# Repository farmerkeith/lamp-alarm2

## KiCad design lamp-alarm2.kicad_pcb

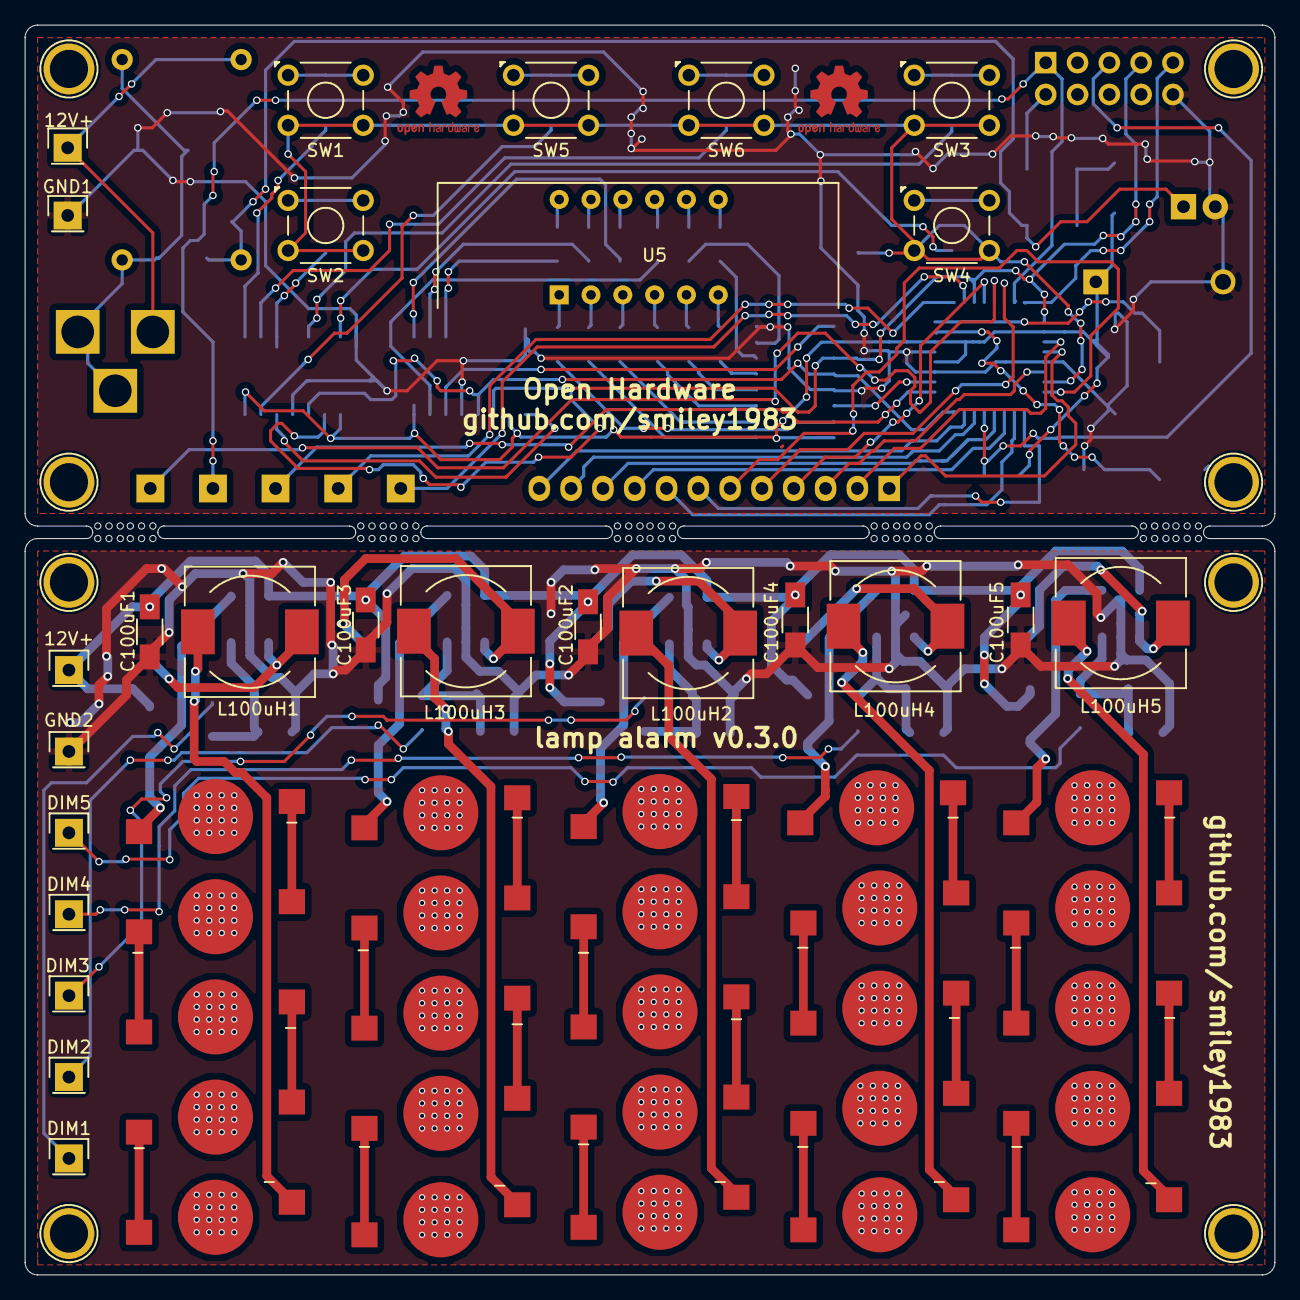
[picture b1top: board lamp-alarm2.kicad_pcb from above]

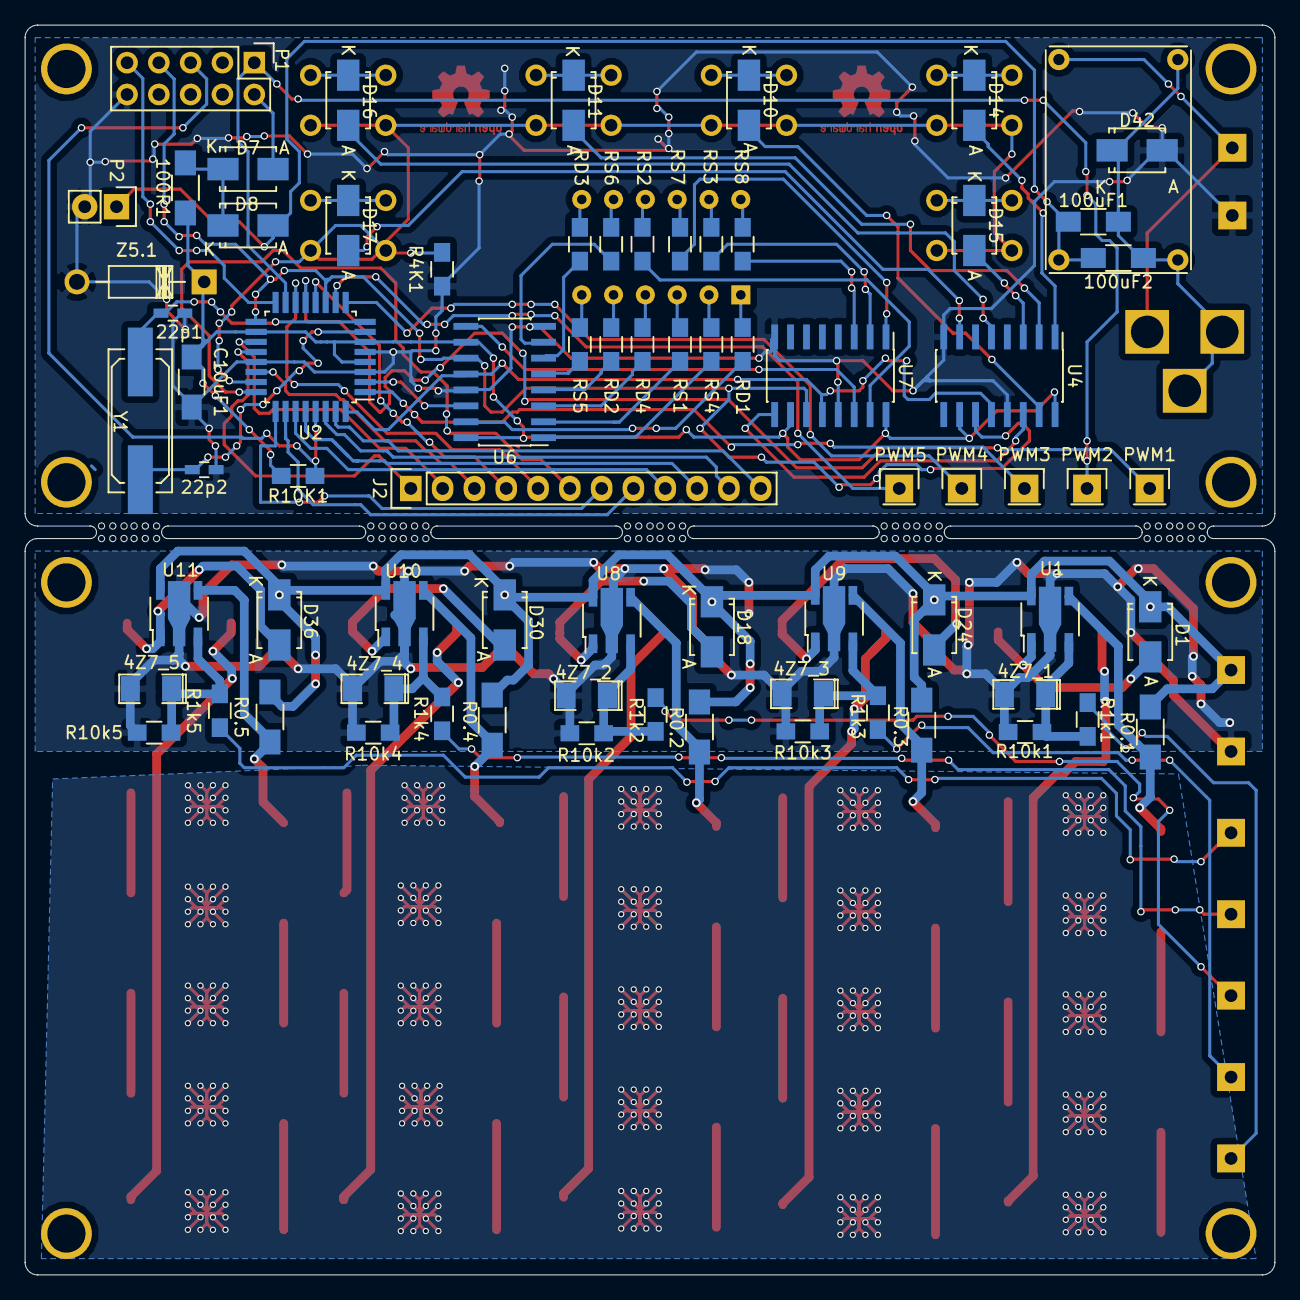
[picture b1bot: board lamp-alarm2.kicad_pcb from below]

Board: 2 copper layers, 99.8 x 99.8 mm, 126 parts (74 on the bottom side), 118 nets.

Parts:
4Z7_1, 4Z7_2, 4Z7_3, 4Z7_4, 4Z7_5: D_Zener_Small; SMD-1206_Pol
12V+, 12V+#2: TEST_1P; Pin_Header_Straight_1x01
22p1, 22p2: C_Small; C_0603_HandSoldering
100R1: R; R_1206_HandSoldering
100uF1, 100uF2: C_Small; C_1206_HandSoldering
-: LED_PAD; 3w_led
-#2, -#3, -#4, -#5, -#6, -#7, -#8, -#9, -#10, -#11, -#12, -#13, -#14, -#15, -#16, -#17, -#18, -#19, -#20, -#21, -#22, -#23, -#24, -#25: LED_PAD; 3w_led
C10uF1, C100uF1, C100uF2, C100uF3, C100uF4, C100uF5: C_Small; C_1206_HandSoldering
D1, D18, D24, D30, D36: D; SMA_Standard_noadhesive
D7, D8, D10, D11, D14, D15, D16, D17, D42: D_Schottky_Small; SMA_Standard_noadhesive
DIM1, DIM2, DIM3, DIM4, DIM5: TEST_1P; Pin_Header_Straight_1x01
GND1, GND2: TEST_1P; Pin_Header_Straight_1x01
J1: Barrel_Jack; BARREL_JACK_nosilk
J2: Conn_01x12; Pin_Header_Straight_1x12
L100uH1, L100uH2, L100uH3, L100uH4, L100uH5: L; Choke_SMD_10.4x10.4_H4.8
P1: CONN_02X05; Pin_Header_Straight_2x05
P2: CONN_01X02; Pin_Header_Straight_1x02
PWM1, PWM2, PWM3, PWM4, PWM5: TEST_1P; Pin_Header_Straight_1x01
R0.1, R0.2, R0.3, R0.4, R0.5: R; R_1206_HandSoldering
R1k1, R1k2, R1k3, R1k4, R1k5, R4K1, R10K1, R10k1, R10k2, R10k3, R10k4, R10k5: R; R_0805_HandSoldering
RD1, RD2, RD3, RD4: R; R_0805_HandSoldering
RS1, RS2, RS3, RS4, RS5, RS6, RS7, RS8: R; R_0805_HandSoldering
SW1, SW2, SW3, SW4, SW5, SW6: SW_PUSH_SMALL_H; tact_switch_6x6
U1, U8, U9, U10, U11: MADW__PT4115-SOT89-5; SOT89-5_Housing
U2: ATMEGA328P-AU; TQFP-32_7x7mm_Pitch0.8mm_narrowerpads
U3: BUCK_1A
U4, U6, U7: 74HC595; SOIC-16_3.9x9.9mm_Pitch1.27mm-narrowerpads
U5: Display_7Seg_Cathode_YY2841AH-33; 7Segment_12pin_1cm_high
Y1: Crystal_Small; Q_49U3HMS
Z5.1: ZENER; Diode_DO-41_SOD81_Horizontal_RM10

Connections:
/HEAT: -.3, -#2.3, -#3.3, -#4.3, -#5.3, -#6.3, -#7.3, -#8.3, -#9.3, -#10.3, -#11.3, -#12.3, -#13.3, -#14.3, -#15.3, -#16.3, -#17.3, -#18.3, -#19.3, -#20.3, -#21.3, -#22.3, -#23.3, -#24.3, -#25.3
/HGND: 4Z7_1.2, 4Z7_2.2, 4Z7_3.2, 4Z7_4.2, 4Z7_5.2, C100uF1.2, C100uF2.2, C100uF3.2, C100uF4.2, C100uF5.2, GND2.1, R10k1.2, R10k2.2, R10k3.2, R10k4.2, R10k5.2, U1.2, U8.2, U9.2, U10.2, U11.2
/LED/LED+: -#25.2, R0.1.1, U1.4
/LED/LED-: -#22.1, L100uH1.1
/PWM0: DIM1.1, R1k1.1
/PWM1: DIM2.1, R1k3.1
/PWM2: DIM3.1, R1k2.1
/PWM3: DIM4.1, R1k4.1
/PWM4: DIM5.1, R1k5.1
/Power/GND_IN: 100uF1.1, 100uF2.1, D42.1, J1.2, J1.3, U3.2, U3.4
/Power/V+: 12V+.1, J1.1, U3.1
/Sheet59CCFEA9/5V_IN: 100uF1.2, 100uF2.2, D8.2, P2.1, U3.3
/Sheet59CCFEA9/ADC6: J2.2, U2.19
/Sheet59CCFEA9/ADC7: J2.3, U2.22
/Sheet59CCFEA9/AREF: J2.1, U2.20
/Sheet59CCFEA9/BTN: R4K1.2, SW1.2, SW2.2, SW3.2, SW4.2, SW5.2, SW6.2, U2.23
/Sheet59CCFEA9/LATCH: U2.32, U4.12, U6.12, U7.12
/Sheet59CCFEA9/MISO: P1.9, U2.16
/Sheet59CCFEA9/PB0: J2.4, U2.12
/Sheet59CCFEA9/PC1: J2.6, U2.24
/Sheet59CCFEA9/PC2: J2.7, U2.25
/Sheet59CCFEA9/PC3: J2.8, U2.26
/Sheet59CCFEA9/PC4: J2.9, U2.27
/Sheet59CCFEA9/PC5: J2.10, U2.28
/Sheet59CCFEA9/PD0: J2.11, U2.30
/Sheet59CCFEA9/PD1: J2.12, U2.31
/Sheet59CCFEA9/PWM0: PWM1.1, U2.13
/Sheet59CCFEA9/PWM1: P1.1, PWM2.1, U2.15
/Sheet59CCFEA9/PWM2: PWM3.1, U2.1
/Sheet59CCFEA9/PWM3: PWM4.1, U2.9
/Sheet59CCFEA9/PWM4: PWM5.1, U2.10
/Sheet59CCFEA9/RST: P1.5, R10K1.1, U2.29
/Sheet59CCFEA9/SS: J2.5, U2.14
/Sheet59CCFEA9/XTAL1: 22p2.2, U2.7, Y1.1
/Sheet59CCFEA9/XTAL2: 22p1.2, U2.8, Y1.2
/UI/CLOCK: P1.7, U2.11, U2.17, U4.11, U6.11, U7.11
/UI/SER_IN: U2.2, U6.14
/UI/sheet57CBF124/AA: RD1.2, U6.15
/UI/sheet57CBF124/AB: RS4.2, U6.1
/UI/sheet57CBF124/AC: RS1.2, U6.2
/UI/sheet57CBF124/AD: RD4.2, U6.3
/UI/sheet57CBF124/AE: RD2.2, U6.4
/UI/sheet57CBF124/AF: RS5.2, U6.5
/UI/sheet57CBF124/AG: RD3.2, U6.6
/UI/sheet57CBF124/AH: RS6.2, U6.7
/UI/sheet57CBF124/BA: RS2.2, U7.15
/UI/sheet57CBF124/BB: RS7.2, U7.1
/UI/sheet57CBF124/BC: RS3.2, U7.2
/UI/sheet57CBF124/BD: RS8.2, U7.3
/UI/sheet57CBF124/SER_OUT: U4.14, U7.9
/V+: 12V+#2.1, C100uF1.1, C100uF2.1, C100uF3.1, C100uF4.1, C100uF5.1, D1.1, D18.1, D24.1, D30.1, D36.1, R0.1.2, R0.2.2, R0.3.2, R0.4.2, R0.5.2, U1.5, U8.5, U9.5, U10.5, U11.5
/sheet59D3A6ED/LED+: -#11.2, R0.4.1, U10.4
/sheet59D3A6ED/LED-: -#7.1, L100uH4.1
/sheet59D3AE4B/LED+: -#6.2, R0.5.1, U11.4
/sheet59D3AE4B/LED-: -#2.1, L100uH5.1
/sheet59D38E92/LED+: -#21.2, R0.2.1, U8.4
/sheet59D38E92/LED-: -#17.1, L100uH2.1
/sheet59D39A20/LED+: -#16.2, R0.3.1, U9.4
/sheet59D39A20/LED-: -#12.1, L100uH3.1
GND: 22p1.1, 22p2.1, C10uF1.2, D42.2, GND1.1, P1.10, P2.2, R4K1.1, U2.3, U2.5, U2.21, U4.8, U4.13, U6.8, U6.13, U7.8, U7.13, Z5.1.2
unnamed: 4Z7_1.1, R1k1.2, R10k1.1, U1.3
unnamed: 4Z7_2.1, R1k2.2, R10k2.1, U8.3
unnamed: 4Z7_3.1, R1k3.2, R10k3.1, U9.3
unnamed: 4Z7_4.1, R1k4.2, R10k4.1, U10.3
unnamed: 4Z7_5.1, R1k5.2, R10k5.1, U11.3
unnamed: 100R1.2, D7.1, D8.1
unnamed: D1.2, L100uH1.2, U1.1
unnamed: -#24.2, -#25.1
unnamed: -.2, -#24.1
unnamed: -.1, -#23.2
unnamed: -#22.2, -#23.1
unnamed: D7.2, P1.2
unnamed: D10.1, SW5.1
unnamed: D10.2, U4.15
unnamed: D11.1, SW6.1
unnamed: D11.2, U4.2
unnamed: D14.1, SW1.1
unnamed: D14.2, U4.1
unnamed: D15.1, SW2.1
unnamed: D15.2, U4.3
unnamed: D16.1, SW3.1
unnamed: D16.2, U4.5
unnamed: D17.1, SW4.1
unnamed: D17.2, U4.7
unnamed: D18.2, L100uH2.2, U8.1
unnamed: -#20.2, -#21.1
unnamed: -#19.2, -#20.1
unnamed: -#18.2, -#19.1
unnamed: -#17.2, -#18.1
unnamed: D24.2, L100uH3.2, U9.1
unnamed: -#15.2, -#16.1
unnamed: -#14.2, -#15.1
unnamed: -#13.2, -#14.1
unnamed: -#12.2, -#13.1
unnamed: D30.2, L100uH4.2, U10.1
unnamed: -#10.2, -#11.1
unnamed: -#9.2, -#10.1
unnamed: -#8.2, -#9.1
unnamed: -#7.2, -#8.1
unnamed: D36.2, L100uH5.2, U11.1
unnamed: -#5.2, -#6.1
unnamed: -#4.2, -#5.1
unnamed: -#3.2, -#4.1
unnamed: -#2.2, -#3.1
unnamed: RD1.1, U5.1
unnamed: RD2.1, U5.5
unnamed: RD3.1, U5.7
unnamed: RD4.1, U5.4
unnamed: RS1.1, U5.3
unnamed: RS2.1, U5.9
unnamed: RS3.1, U5.11
unnamed: RS4.1, U5.2
unnamed: RS5.1, U5.6
unnamed: RS6.1, U5.8
unnamed: RS7.1, U5.10
unnamed: RS8.1, U5.12
unnamed: U6.9, U7.14
VCC: 100R1.1, C10uF1.1, R10K1.2, U2.4, U2.6, U2.18, U4.10, U4.16, U6.10, U6.16, U7.10, U7.16, Z5.1.1

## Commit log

2017-10-07 import board submission status
2017-10-07 add gitignore
